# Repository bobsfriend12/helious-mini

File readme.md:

## Helious Mini Macropad

I designed this macropad to be used with my ETC Nomad to program lights. You can configure the QMK firmware to be any eos key you need by looking up the keyboard shortcut.

## BOM

This design requires the following components to build:

-   15x Cherry style switches
-   1 Rotary Encoder
-   15x SK6812MINI LEDS
-   16x Through-hole 1N4148 Diodes
-   1x Seeed XIAO RP2040

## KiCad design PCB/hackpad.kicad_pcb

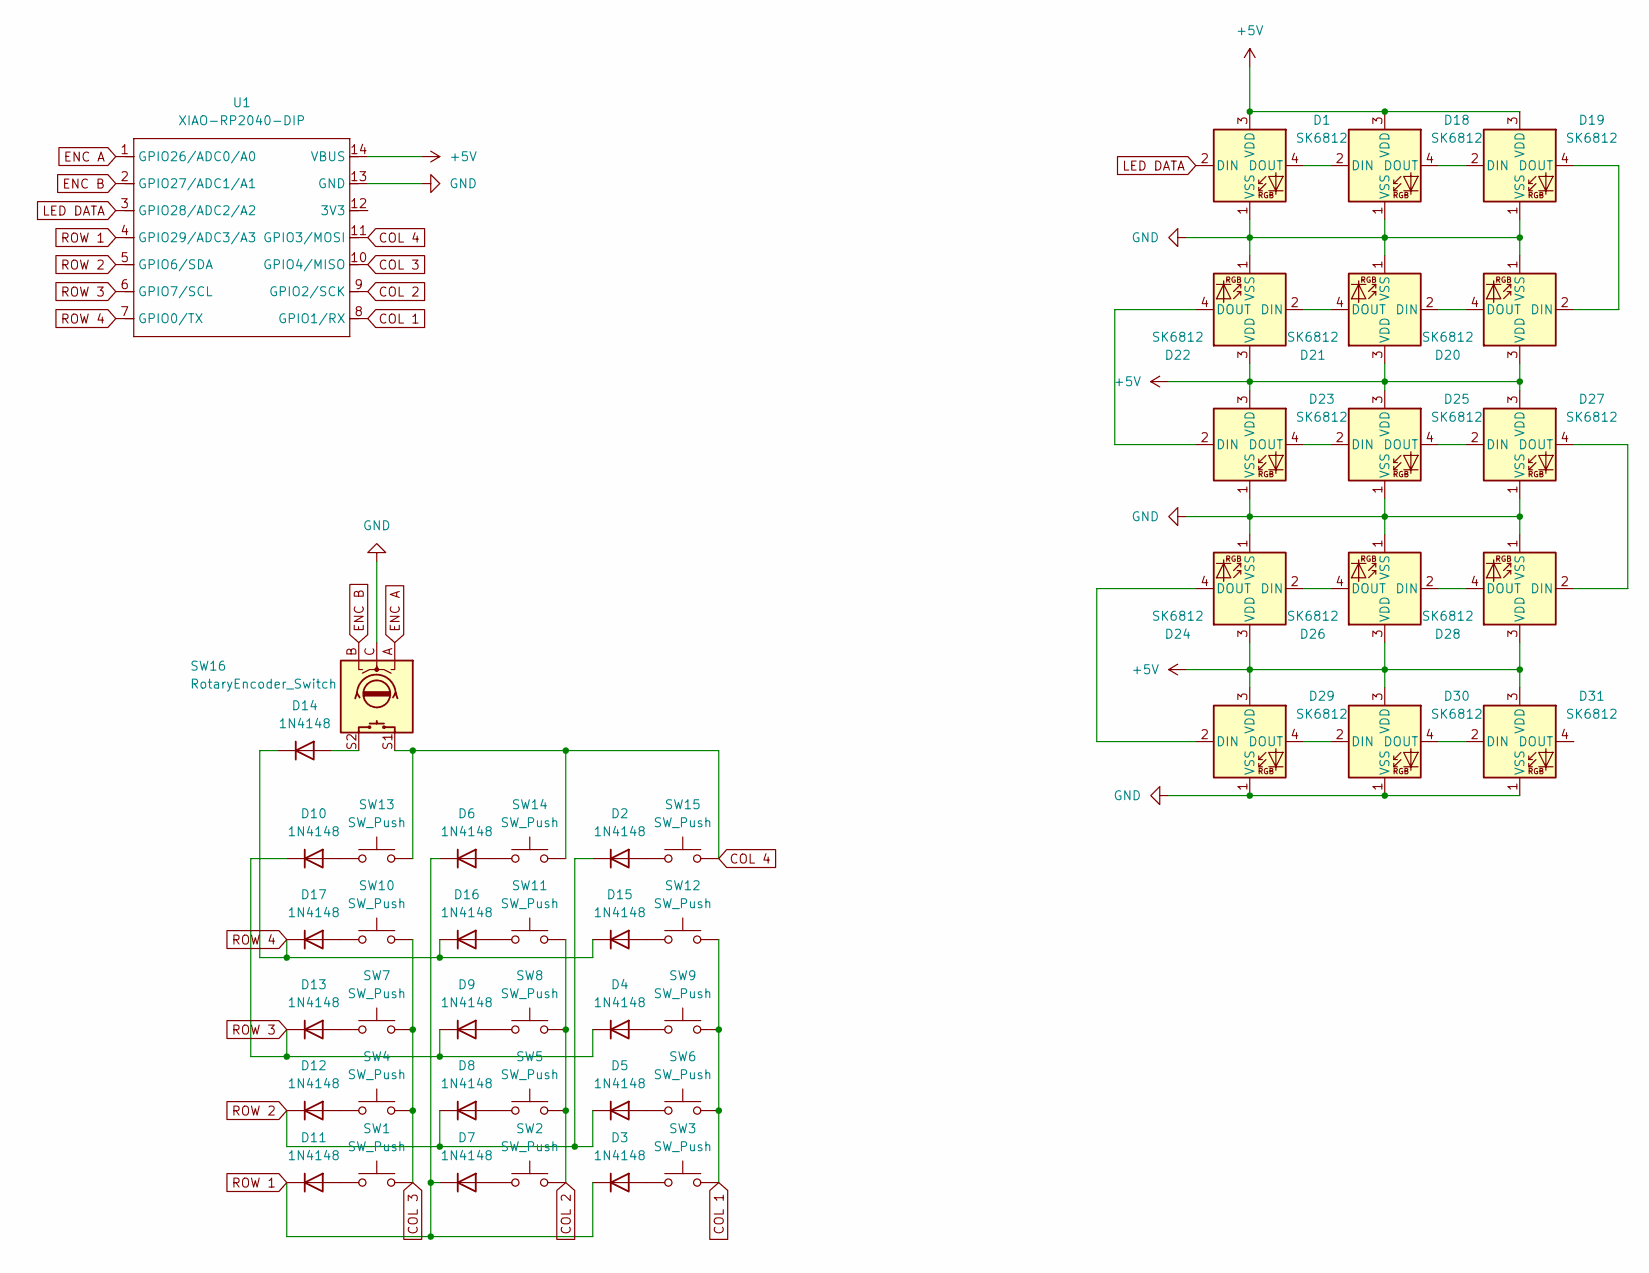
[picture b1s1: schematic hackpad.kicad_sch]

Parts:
D1, D18, D19, D20, D21, D22, D23, D24, D25, D26, D27, D28, D29, D30, D31: SK6812; LED_SK6812MINI_PLCC4_3.5x3.5mm_P1.75mm
D2, D3, D4, D5, D6, D7, D8, D9, D10, D11, D12, D13, D14, D15, D16, D17: 1N4148; D_DO-35_SOD27_P7.62mm_Horizontal
SW1, SW2, SW3, SW4, SW5, SW6, SW7, SW8, SW9, SW10, SW11, SW12, SW13, SW14, SW15: SW_Push; SW_Cherry_MX_1.00u_PCB
SW16: RotaryEncoder_Switch; RotaryEncoder_Alps_EC11E-Switch_Vertical_H20mm
U1: XIAO-RP2040-DIP; XIAO-RP2040-SMD

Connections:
+5V: D1.3 (VDD), D18.3 (VDD), D19.3 (VDD), D20.3 (VDD), D21.3 (VDD), D22.3 (VDD), D23.3 (VDD), D24.3 (VDD), D25.3 (VDD), D26.3 (VDD), D27.3 (VDD), D28.3 (VDD), D29.3 (VDD), D30.3 (VDD), D31.3 (VDD), U1.14 (VBUS)
COL 1: SW3.2, SW6.2, SW9.2, SW12.2, U1.8 (GPIO1/RX)
COL 2: SW2.2, SW5.2, SW8.2, SW11.2, U1.9 (GPIO2/SCK)
COL 3: SW1.2, SW4.2, SW7.2, SW10.2, U1.10 (GPIO4/MISO)
COL 4: SW13.2, SW14.2, SW15.2, SW16.S1, U1.11 (GPIO3/MOSI)
ENC A: SW16.A, U1.1 (GPIO26/ADC0/A0)
ENC B: SW16.B, U1.2 (GPIO27/ADC1/A1)
GND: D1.1 (VSS), D18.1 (VSS), D19.1 (VSS), D20.1 (VSS), D21.1 (VSS), D22.1 (VSS), D23.1 (VSS), D24.1 (VSS), D25.1 (VSS), D26.1 (VSS), D27.1 (VSS), D28.1 (VSS), D29.1 (VSS), D30.1 (VSS), D31.1 (VSS), SW16.C, U1.13 (GND)
LED DATA: D1.2 (DIN), U1.3 (GPIO28/ADC2/A2)
unnamed: D1.4 (DOUT), D18.2 (DIN)
unnamed: D2.2 (A), SW15.1
unnamed: D3.2 (A), SW3.1
unnamed: D4.2 (A), SW9.1
unnamed: D5.2 (A), SW6.1
unnamed: D6.2 (A), SW14.1
unnamed: D7.2 (A), SW2.1
unnamed: D8.2 (A), SW5.1
unnamed: D9.2 (A), SW8.1
unnamed: D10.2 (A), SW13.1
unnamed: D11.2 (A), SW1.1
unnamed: D12.2 (A), SW4.1
unnamed: D13.2 (A), SW7.1
unnamed: D14.2 (A), SW16.S2
unnamed: D15.2 (A), SW12.1
unnamed: D16.2 (A), SW11.1
unnamed: D17.2 (A), SW10.1
unnamed: D18.4 (DOUT), D19.2 (DIN)
unnamed: D19.4 (DOUT), D20.2 (DIN)
unnamed: D20.4 (DOUT), D21.2 (DIN)
unnamed: D21.4 (DOUT), D22.2 (DIN)
unnamed: D22.4 (DOUT), D23.2 (DIN)
unnamed: D23.4 (DOUT), D25.2 (DIN)
unnamed: D24.2 (DIN), D26.4 (DOUT)
unnamed: D24.4 (DOUT), D29.2 (DIN)
unnamed: D25.4 (DOUT), D27.2 (DIN)
unnamed: D26.2 (DIN), D28.4 (DOUT)
unnamed: D27.4 (DOUT), D28.2 (DIN)
unnamed: D29.4 (DOUT), D30.2 (DIN)
unnamed: D30.4 (DOUT), D31.2 (DIN)
ROW 1: D3.1 (K), D6.1 (K), D7.1 (K), D11.1 (K), U1.4 (GPIO29/ADC3/A3)
ROW 2: D2.1 (K), D5.1 (K), D8.1 (K), D12.1 (K), U1.5 (GPIO6/SDA)
ROW 3: D4.1 (K), D9.1 (K), D10.1 (K), D13.1 (K), U1.6 (GPIO7/SCL)
ROW 4: D14.1 (K), D15.1 (K), D16.1 (K), D17.1 (K), U1.7 (GPIO0/TX)

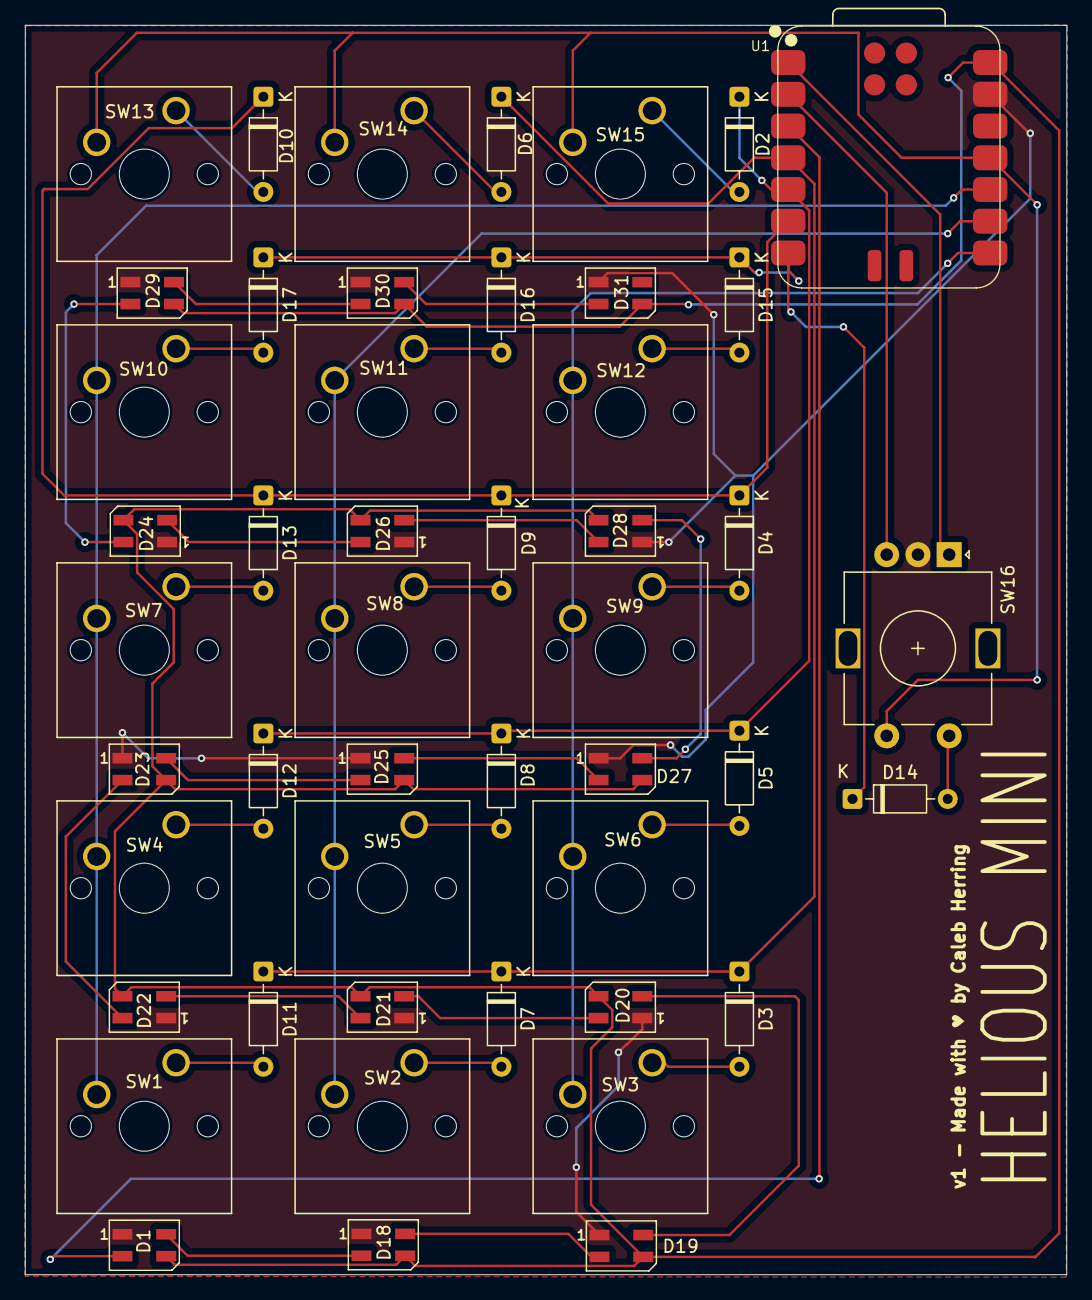
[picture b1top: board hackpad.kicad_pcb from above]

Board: 2 copper layers, 83.3 x 100.0 mm, 48 parts (0 on the bottom side), 43 nets.

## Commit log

2026-01-14 add readme
2026-01-14 fix images
2026-01-14 remoe ds store
2026-01-14 Add firmware
2026-01-15 update CAD
